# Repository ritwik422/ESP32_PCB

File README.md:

# ESP32_PCB

# A pcb using espressif ESP32-S3-DEV
This project involves making a devboard using the ESP32-s3 module by Espressif.
We know ESP are the go-to microcontrollers when we want speed and integrated Wifi Bluetooth in out projects.

# Features
1. Fully designed in KiCad
2. Features a USB-C USB 2.0 for convenience
3. ESP32 DevBoard features a design under 100*100mm, making it ideal for production houses.
4. 2-Layer PCB
5. Built in AdaFruit NeoPixel as an actuator
6. Built in Zero-PCB/protoboard with ~600 holes to make deployment after prorotype as easy as it can get!

# Main components used
1. Espressif ESP32-S3-Mini-N8
2. Adafruit Neopixel 5mm
3. Texas Instruments tlv758p
4. USB-C 2.0

# Schematic
Designed in KiCad

# resources I used for this project:
1. https://docs.espressif.com/projects/esp-hardware-design-guidelines/en/latest/esp32s3/esp-hardware-design-guidelines-en-master-esp32s3.pdf
2. https://docs.espressif.com/projects/esp-idf/en/stable/esp32s3/get-started/index.html
3. https://www.ti.com/lit/ds/symlink/tlv758p.pdf?ts=1764750861284
4. https://documentation.espressif.com/esp32-s3_technical_reference_manual_en.pdf
5. https://cdn-shop.adafruit.com/datasheets/WS2812B.pdf

# Credits & Inspiration
This project was built as an improved version of an existing tutorial/project by **John Teel**, Founder / Engineer at [Predictable Designs](https://predictabledesigns.com/).

# Developer note:
If you do manufacture this PCB, when you get it for the first time, it is necessary to do the initialization boot sequence when esp is powered.
hold boot> click reset once> release boot
This allows ESP to go into coding mode where you can upload code into your board.

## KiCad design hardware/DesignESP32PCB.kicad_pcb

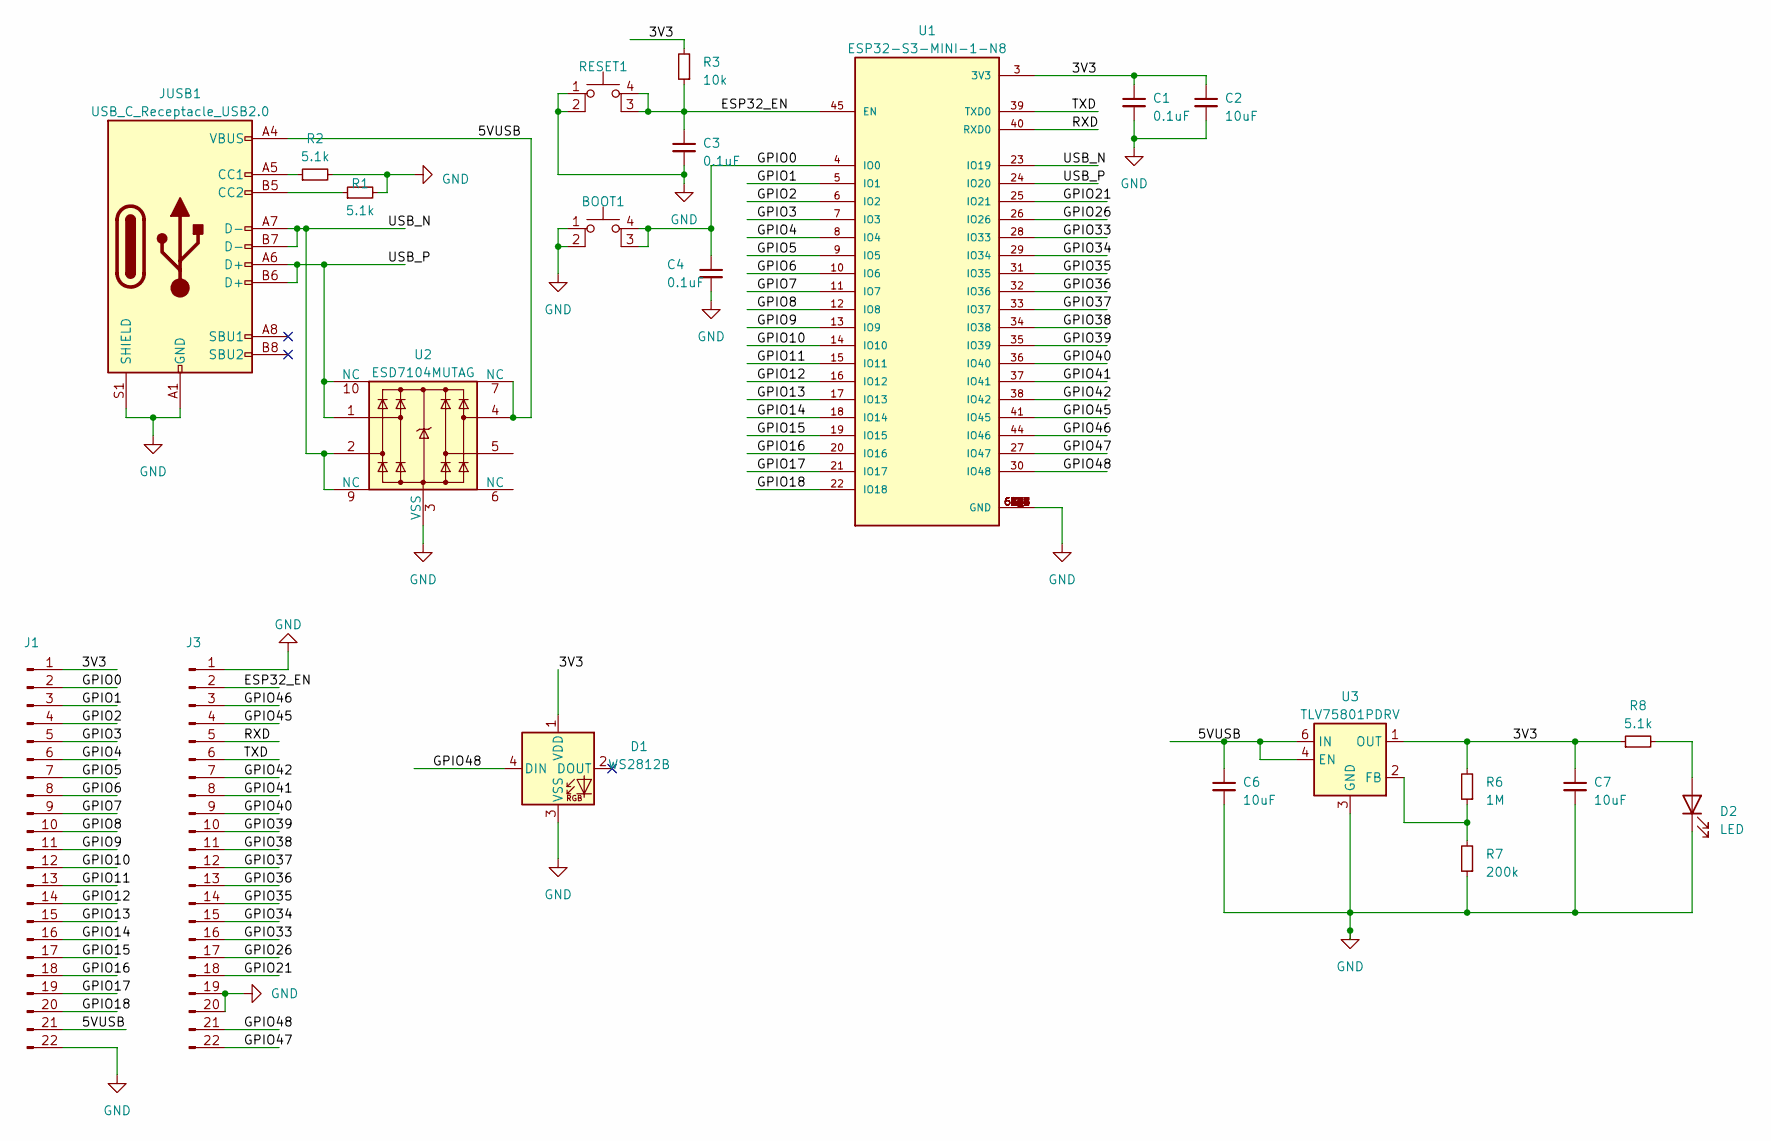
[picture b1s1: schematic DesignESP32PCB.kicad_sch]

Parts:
BOOT1: SW_SPST_PTS810
C1, C3, C4: 0.1uF; C_0603_1608Metric
C2, C6, C7: 10uF; C_0603_1608Metric
D1: WS2812B; LED_WS2812B_PLCC4_5.0x5.0mm_P3.2mm
D2: LED; LED_0603_1608Metric
J1, J3: PinHeader_1x22_P2.54mm_Vertical
JUSB1: USB_C_Receptacle_USB2.0; USB_C_Receptacle_GCT_USB4105-xx-A_16P_TopMnt_Horizontal
R1, R2, R8: 5.1k; R_0603_1608Metric
R3: 10k; R_0603_1608Metric
R6: 1M; R_0603_1608Metric
R7: 200k; R_0603_1608Metric
RESET1: SW_SPST_PTS810
U1: ESP32-S3-MINI-1-N8; XCVR_ESP32-S3-MINI-1-N8; PARTREV v0.6
U2: ESD7104MUTAG; Diodes_UDFN-10_1.0x2.5mm_P0.5mm
U3: TLV75801PDRV; WSON-6-1EP_2x2mm_P0.65mm_EP1x1.6mm

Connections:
/3V3: C1.1, C2.1, C7.1, D1.1 (VDD), J1.1, R3.2, R6.2, R8.1, U1.3 (3V3), U3.1 (OUT)
/5VUSB: C6.1, J1.21, JUSB1.A4 (VBUS), JUSB1.A9 (VBUS), JUSB1.B4 (VBUS), JUSB1.B9 (VBUS), U2.4, U2.7 (NC), U3.4 (EN), U3.6 (IN)
/ESP32_EN: C3.1, J3.2, R3.1, RESET1.3 (K), RESET1.4 (A), U1.45 (EN); also elsewhere on the board
/GPIO0: BOOT1.3 (K), BOOT1.4 (A), C4.1, J1.2, U1.4 (IO0); also elsewhere on the board
/GPIO1: J1.3, U1.5 (IO1)
/GPIO2: J1.4, U1.6 (IO2)
/GPIO3: J1.5, U1.7 (IO3)
/GPIO4: J1.6, U1.8 (IO4)
/GPIO5: J1.7, U1.9 (IO5)
/GPIO6: J1.8, U1.10 (IO6)
/GPIO7: J1.9, U1.11 (IO7)
/GPIO8: J1.10, U1.12 (IO8)
/GPIO9: J1.11, U1.13 (IO9)
/GPIO10: J1.12, U1.14 (IO10)
/GPIO11: J1.13, U1.15 (IO11)
/GPIO12: J1.14, U1.16 (IO12)
/GPIO13: J1.15, U1.17 (IO13)
/GPIO14: J1.16, U1.18 (IO14)
/GPIO15: J1.17, U1.19 (IO15)
/GPIO16: J1.18, U1.20 (IO16)
/GPIO17: J1.19, U1.21 (IO17)
/GPIO18: J1.20, U1.22 (IO18)
/GPIO21: J3.18, U1.25 (IO21)
/GPIO26: J3.17, U1.26 (IO26)
/GPIO33: J3.16, U1.28 (IO33)
/GPIO34: J3.15, U1.29 (IO34)
/GPIO35: J3.14, U1.31 (IO35)
/GPIO36: J3.13, U1.32 (IO36)
/GPIO37: J3.12, U1.33 (IO37)
/GPIO38: J3.11, U1.34 (IO38)
/GPIO39: J3.10, U1.35 (IO39)
/GPIO40: J3.9, U1.36 (IO40)
/GPIO41: J3.8, U1.37 (IO41)
/GPIO42: J3.7, U1.38 (IO42)
/GPIO45: J3.4, U1.41 (IO45)
/GPIO46: J3.3, U1.44 (IO46)
/GPIO47: J3.22, U1.27 (IO47)
/GPIO48: D1.4 (DIN), J3.21, U1.30 (IO48)
/RXD: J3.5, U1.40 (RXD0)
/TXD: J3.6, U1.39 (TXD0)
/USB_N: JUSB1.A7 (D-), JUSB1.B7 (D-), U1.23 (IO19), U2.2, U2.9 (NC)
/USB_P: JUSB1.A6 (D+), JUSB1.B6 (D+), U1.24 (IO20), U2.1, U2.10 (NC)
GND: BOOT1.1, BOOT1.2, C1.2, C2.2, C3.2, C4.2, C6.2, C7.2, D1.3 (VSS), D2.1 (K), J1.22, J3.1, J3.19, J3.20, JUSB1.A1 (GND), JUSB1.A12 (GND), JUSB1.B1 (GND), JUSB1.B12 (GND), JUSB1.S1 (SHIELD), R1.2, R2.2, R7.1, RESET1.1, RESET1.2, U1.1 (GND), U1.2 (GND), U1.42 (GND), U1.43 (GND), U1.46 (GND), U1.47 (GND), U1.48 (GND), U1.49 (GND), U1.50 (GND), U1.51 (GND), U1.52 (GND), U1.53 (GND), U1.54 (GND), U1.55 (GND), U1.56 (GND), U1.57 (GND), U1.58 (GND), U1.59 (GND), U1.60 (GND), U1.61 (GND), U1.61_1 (GND), U1.61_2 (GND), U1.61_3 (GND), U1.61_4 (GND), U1.61_5 (GND), U1.61_6 (GND), U1.61_7 (GND), U1.61_8 (GND), U1.62 (GND), U1.63 (GND), U1.64 (GND), U1.65 (GND), U2.3 (VSS), U2.8 (VSS), U3.3 (GND), U3.7 (GND); also elsewhere on the board
unnamed: D2.2 (A), R8.2
unnamed: JUSB1.A5 (CC1), R2.1
unnamed: JUSB1.B5 (CC2), R1.1
unnamed: R6.1, R7.2, U3.2 (FB)

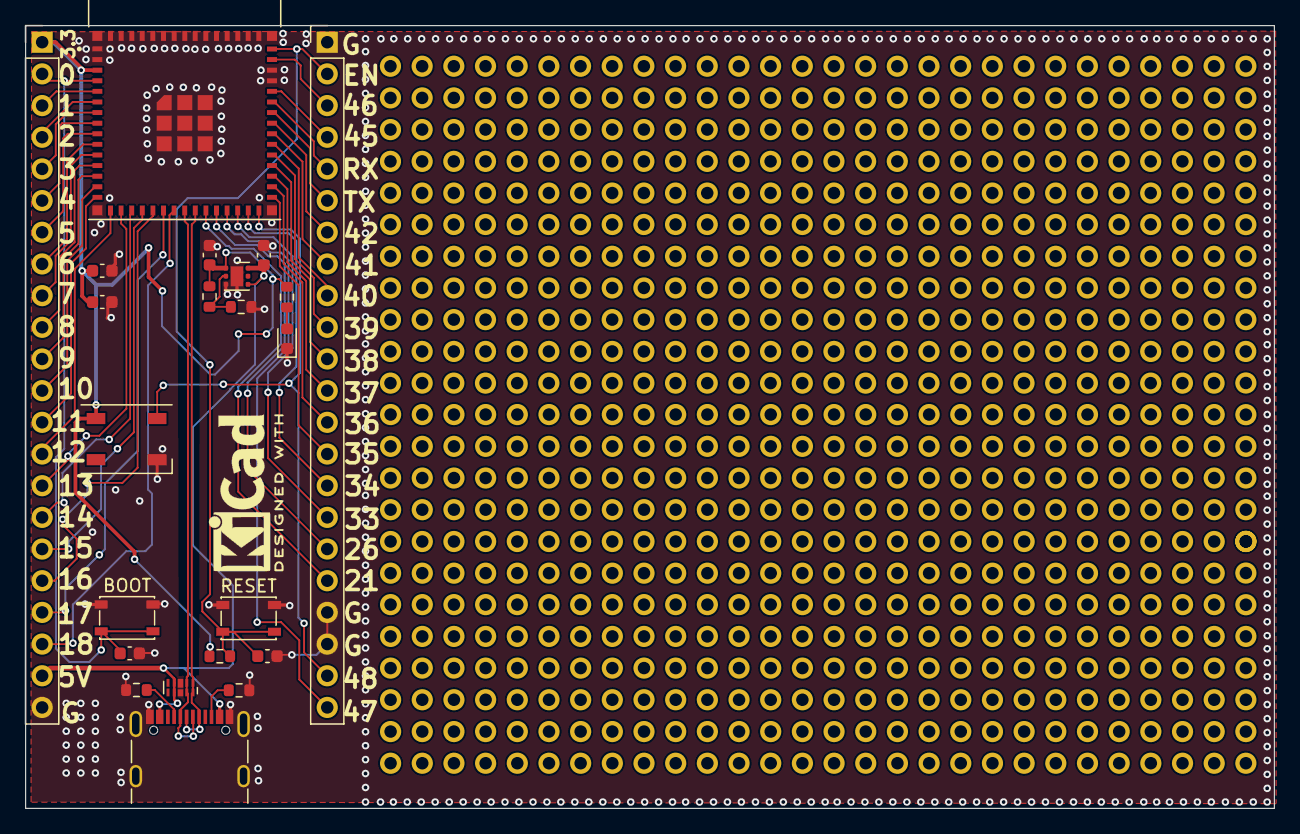
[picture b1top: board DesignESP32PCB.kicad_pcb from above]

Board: 2 copper layers, 100.1 x 62.8 mm, 22 parts (0 on the bottom side), 47 nets.

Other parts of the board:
BOOT: SW_SPST_PTS810
RESET: SW_SPST_PTS810

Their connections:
/ESP32_EN: RESET.3 (K), RESET.4 (A); also elsewhere on the board
/GPIO0: BOOT.3 (K), BOOT.4 (A); also elsewhere on the board
GND: BOOT.1, BOOT.2, RESET.1, RESET.2; also elsewhere on the board

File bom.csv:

Designator,Footprint,Quantity,Value,LCSC Part #
"_645, _644, _643, _642, _641, _640, _639, _638, _637, _636, _635, _634, _633, _632, _631, _630, _629, _628, _627, _626, _625, _624, _623, _622, _621, _620, _619, _618, _617, _616, _615, _614, _613, _612, _611, _610, _609, _608, _607, _606, _605, _604, _603, _602, _601, _600, _599, _598, _597, _596, _595, _594, _593, _592, _591, _590, _589, _588, _587, _586, _585, _584, _583, _582, _581, _580, _579, _578, _577, _576, _575, _574, _573, _572, _571, _570, _569, _568, _567, _566, _565, _564, _563, _562, _561, _560, _559, _558, _557, _556, _555, _554, _553, _552, _551, _550, _549, _548, _547, _546, _545, _544, _543, _542, _541, _540, _539, _538, _537, _536, _535, _534, _533, _532, _531, _530, _529, _528, _527, _526, _525, _524, _523, _522, _521, _520, _519, _518, _517, _516, _515, _514, _513, _512, _511, _510, _509, _508, _507, _506, _505, _504, _503, _502, _501, _500, _499, _498, _497, _496, _495, _494, _493, _492, _491, _490, _489, _488, _487, _486, _485, _484, _483, _482, _481, _480, _479, _478, _477, _476, _475, _474, _473, _472, _471, _470, _469, _468, _467, _466, _465, _464, _463, _462, _461, _460, _459, _458, _457, _456, _455, _454, _453, _452, _451, _450, _449, _448, _447, _446",,200,,
"_445, _444, _443, _442, _441, _440, _439, _438, _437, _436, _435, _434, _433, _432, _431, _430, _429, _428, _427, _426, _425, _424, _423, _422, _421, _420, _419, _418, _417, _416, _415, _414, _413, _412, _411, _410, _409, _408, _407, _406, _405, _404, _403, _402, _401, _400, _399, _398, _397, _396, _395, _394, _393, _392, _391, _390, _389, _388, _387, _386, _385, _384, _383, _382, _381, _380, _379, _378, _377, _376, _375, _374, _373, _372, _371, _370, _369, _368, _367, _366, _365, _364, _363, _362, _361, _360, _359, _358, _357, _356, _355, _354, _353, _352, _351, _350, _349, _348, _347, _346, _345, _344, _343, _342, _341, _340, _339, _338, _337, _336, _335, _334, _333, _332, _331, _330, _329, _328, _327, _326, _325, _324, _323, _322, _321, _320, _319, _318, _317, _316, _315, _314, _313, _312, _311, _310, _309, _308, _307, _306, _305, _304, _303, _302, _301, _300, _299, _298, _297, _296, _295, _294, _293, _292, _291, _290, _289, _288, _287, _286, _285, _284, _283, _282, _281, _280, _279, _278, _277, _276, _275, _274, _273, _272, _271, _270, _269, _268, _267, _266, _265, _264, _263, _262, _261, _260, _259, _258, _257, _256, _255, _254, _253, _252, _251, _250, _249, _248, _247, _246",,200,,
"_245, _244, _243, _242, _241, _240, _239, _238, _237, _236, _235, _234, _233, _232, _231, _230, _229, _228, _227, _226, _225, _224, _223, _222, _221, _220, _219, _218, _217, _216, _215, _214, _213, _212, _211, _210, _209, _208, _207, _206, _205, _204, _203, _202, _201, _200, _199, _198, _197, _196, _195, _194, _193, _192, _191, _190, _189, _188, _187, _186, _185, _184, _183, _182, _181, _180, _179, _178, _177, _176, _175, _174, _173, _172, _171, _170, _169, _168, _167, _166, _165, _164, _163, _162, _161, _160, _159, _158, _157, _156, _155, _154, _153, _152, _151, _150, _149, _148, _147, _146, _145, _144, _143, _142, _141, _140, _139, _138, _137, _136, _135, _134, _133, _132, _131, _130, _129, _128, _127, _126, _125, _124, _123, _122, _121, _120, _119, _118, _117, _116, _115, _114, _113, _112, _111, _110, _109, _108, _107, _106, _105, _104, _103, _102, _101, _100, _99, _98, _97, _96, _95, _94, _93, _92, _91, _90, _89, _88, _87, _86, _85, _84, _83, _82, _81, _80, _79, _78, _77, _76, _75, _74, _73, _72, _71, _70, _69, _68, _67, _66, _65, _64, _63, _62, _61, _60, _59, _58, _57, _56, _55, _54, _53, _52, _51, _50, _49, _48, _47, _46",,200,,
"_45, _44, _43, _42, _41, _40, _39, _38, _37, _36, _35, _34, _33, _32, _31, _30, _29, _28, _27, _26, _25, _24, _23, _22, _21, _20, _19, _18, _17, _16, _15, _14, _13, _12, _11, _10, _9, _8, _7, _6, _5, _4, _3, _2, ",,45,,
"BOOT, RESET",SW_SPST_PTS810,2,~,
"C1, C3, C4",0603,3,0.1uF,
"C2, C6, C7",0603,3,10uF,
D1,LED_WS2812B_PLCC4_5.0x5.0mm_P3.2mm,1,WS2812B,
D2,0603,1,LED,
"J1, J3",PinHeader_1x22_P2.54mm_Vertical,2,~,
JUSB1,USB_C_Receptacle_GCT_USB4105-xx-A_16P_TopMnt_Horizontal,1,USB_C_Receptacle_USB2.0,
"R1, R2, R8",0603,3,5.1k,
R3,0603,1,10k,
R6,0603,1,1M,
R7,0603,1,200k,
U1,XCVR_ESP32-S3-MINI-1-N8,1,ESP32-S3-MINI-1-N8,
U2,Diodes_UDFN-10_1.0x2.5mm_P0.5mm,1,ESD7104MUTAG,
U3,WSON-6-1EP_2x2mm_P0.65mm_EP1x1.6mm,1,TLV75801PDRV,

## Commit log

2026-03-07 Restructured repository and added .gitignore
2026-03-07 Moved KiCad project files back to root for easier access, keeping subdirectories for docs, libraries, and manufacturing
2026-03-07 Update README with credits to John Teel
